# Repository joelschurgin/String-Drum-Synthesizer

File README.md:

# String-Drum-Synthesizer

## Problem
A musical artist brings with them a sense of how to evoke certain emotions or create particular atmospheres, but may lack the technical knowledge to bring it to life. Sound design can be challenging as it involves crafting the unique timbres and textures that define a piece of music, which can be both an art and a science. The learning curve is steep, not only because it requires a grasp of complex technical tools but also because it demands a creative intuition that isn't easily taught. Musicians and producers must learn to navigate a vast array of software and hardware tools, each with its own set of knobs, sliders, and buttons. Understanding how to shape sounds means diving deep into the physics of sound waves, the principles of digital signal processing, and the subtleties of different synthesis methods. This process can feel overwhelming, especially for beginners who might feel lost amidst the jargon and the sheer number of options.

## Solution
Build a synthesizer. The range of sounds are controlled by a set of parameters such as filter cutoffs, oscillator types, low frequency oscillators, etc. The proposed solution is two-fold. The first part of the project is to build emotive knobs that feature descriptive ranges such as soft to aggressive or thin to thick. These knobs would also control the internal parameters of the system to achieve the desired effects on the input sound. The other part is to create a system that records a sound and finds the best way to set the synthesizer's internal parameters to recreate it. The intended work flow of this device for a musical artist is to record a sound, tweak the knobs, and play that sound by pressing a key on a MIDI keyboard. It is up to the musician to record the sound into their own recording software for further manipulation.

# Solution Components
## Subsystem 1: Software Synthesizer
Purpose/Requirements: This subsystem will generate sounds using the Karplus Strong algorithm which features a pulse generator and an echo chamber (modeled with digital delay, feedback, and filtering). When a note is played on a USB keyboard, this component must be able to change the pitch based on which key is pressed. The algorithm’s parameters must be controllable using potentiometers, but several parameters can be determined as a function of one knob. We chose the Karplus Strong algorithm to reduce the computational load, but we are modifying certain aspects to allow for a greater range of sounds. The pulse that we will use is a blend of noise and sine wave oscillator which are added together and distorted. In addition, there will be some soft distortion applied on the output. In addition, the echo chamber will use 3 IIR filters: highpass, lowpass, and a bell. The choice to use IIR filters is to lower the amount of computation.

We made a demo of the synthesizer algorithm using a digital audio workstation in order to play with parameters and determine the names of the emotive knobs. Below are the emotive knobs and how the corresponding synth parameters should change to implement them:

Aggression

- Synth Params: Pulse distortion, output distortion
- Knob Left: Low distortion
- Knob Right: High distortion

Brightness

- Synth Param: Low pass filter cutoff
- Knob Left: 20 Hz
- Knob Right: 20 kHz

Boominess

- Synth Param: High pass Cutoff
- Knob Left: 20 kHz
- Knob Center: Note pitch
- Knob Right: 20 Hz

Dampening

- Synth Param: Bell Q
- Knob Left: High Q
- Knob Right: Low Q

*Not sure what to call this yet, but it affects how the echo chamber resonates. Note: setting this to around 3.6 kHz sounds good, so it could be fine to keep this completely internal and forgo the corresponding knob.

- Synth Param: Bell frequency
- Knob Left: 20 hz
- Knob Right: 20 kHz

Scratchiness

- Synth Param: Length of pulse
- Knob Left: 0
- Knob Center: 1/(Note pitch)
- Knob Right: 4/(Note pitch)

Sharpness

- Synth Param: Mix between pulse noise and oscillator
- Knob Left: Pulse consists of only oscillator
- Knob Right: Pulse consists of only noise

*Strike weight => Corresponds to simulated weight of object striking the string/drum head.

- Synth Param: Pulse oscillator pitch
- Knob Left: 20 kHz
- Knob Right: 20 hz

Notes:
- The value "note pitch" is determined by USB keyboard input.
- Bell gain is fixed and should be set to attenuate the signal.

Components:

- Microprocessor
- DAC
- Potentiometers for parameters (linear, should be able to snap to center position if center value has meaning other should be smooth all the way through)
- USB Port

## Subsystem 3: Amplifier
Purpose/Requirements: This subsystem should output the smallest possible signal to noise ratio through a guitar cable or headphones. In order to achieve this we will experiment with using several inverting op-amp amplifier circuits in parallel and summing them together with an inverting mixer. The gain of each amplifier will be set, but the volume control will be part of the inverting mixer circuit.

Components:

- Mono 1/4in audio jack
- 4 Op-amps
- Logarithmic Potentiometer (for volume control)

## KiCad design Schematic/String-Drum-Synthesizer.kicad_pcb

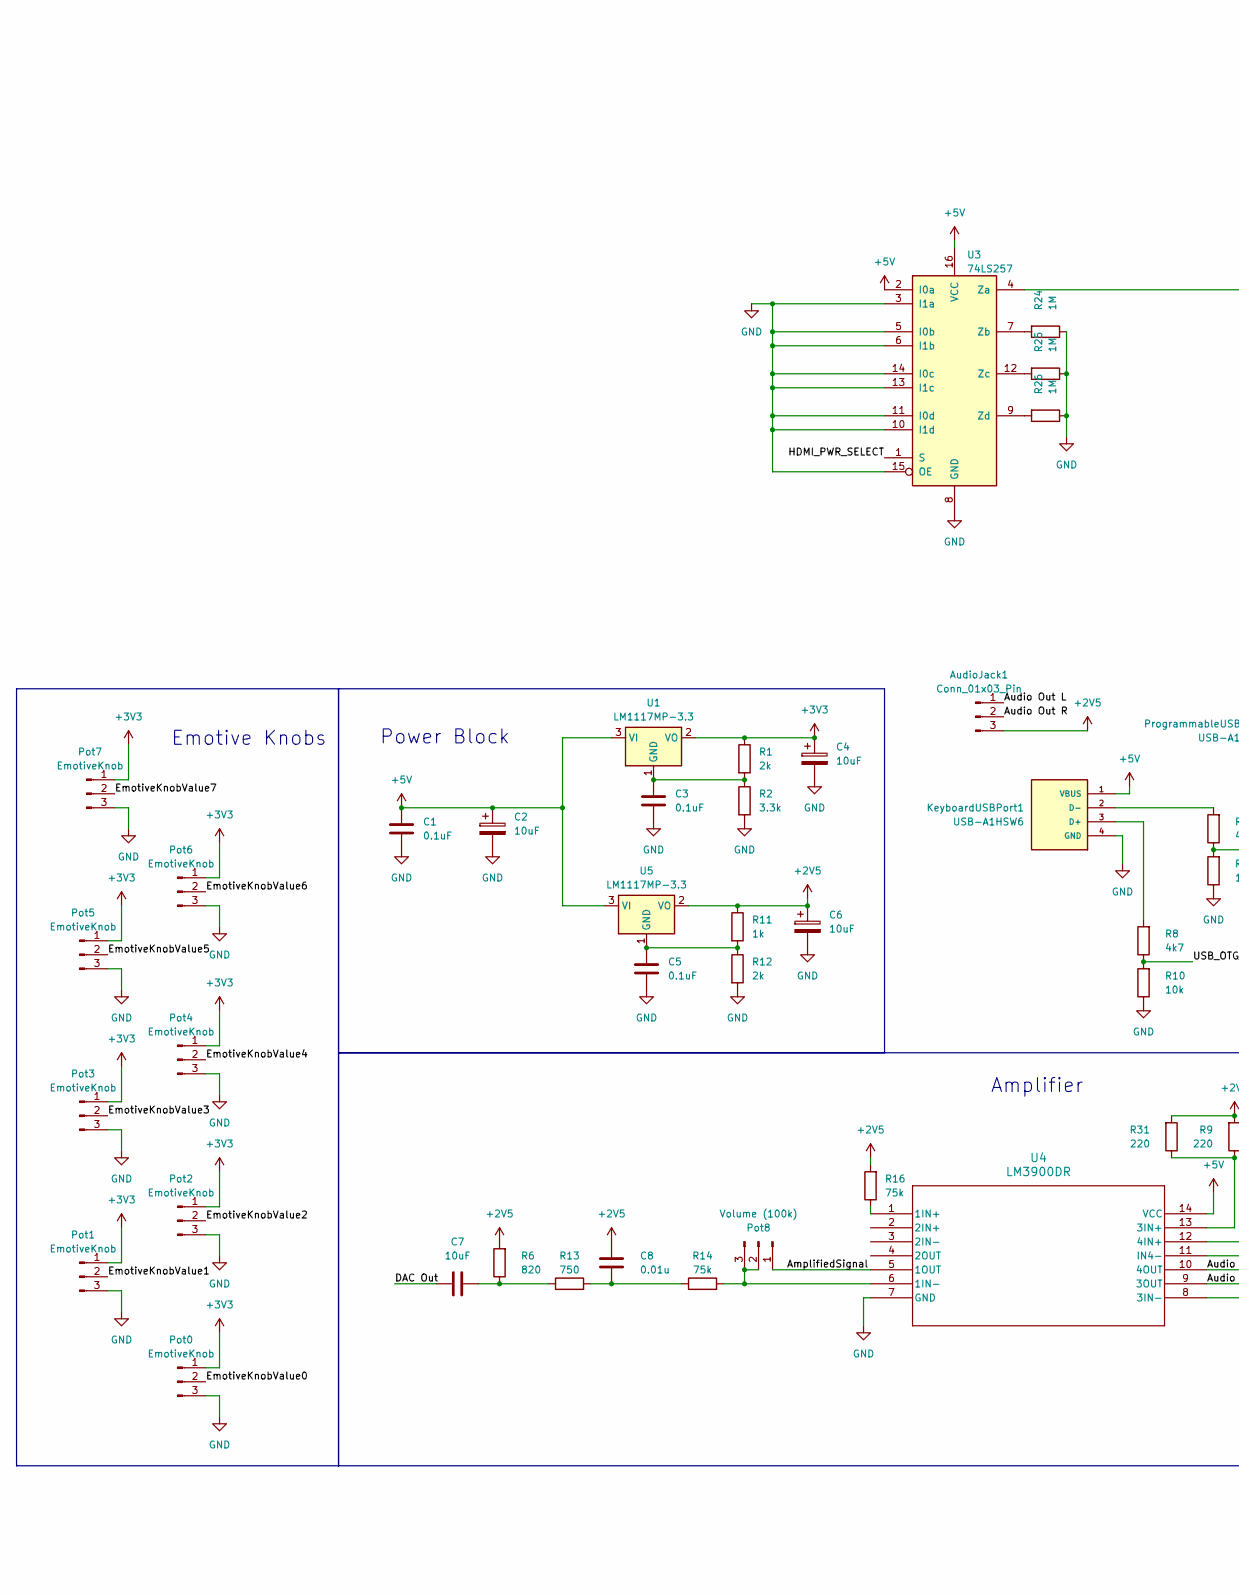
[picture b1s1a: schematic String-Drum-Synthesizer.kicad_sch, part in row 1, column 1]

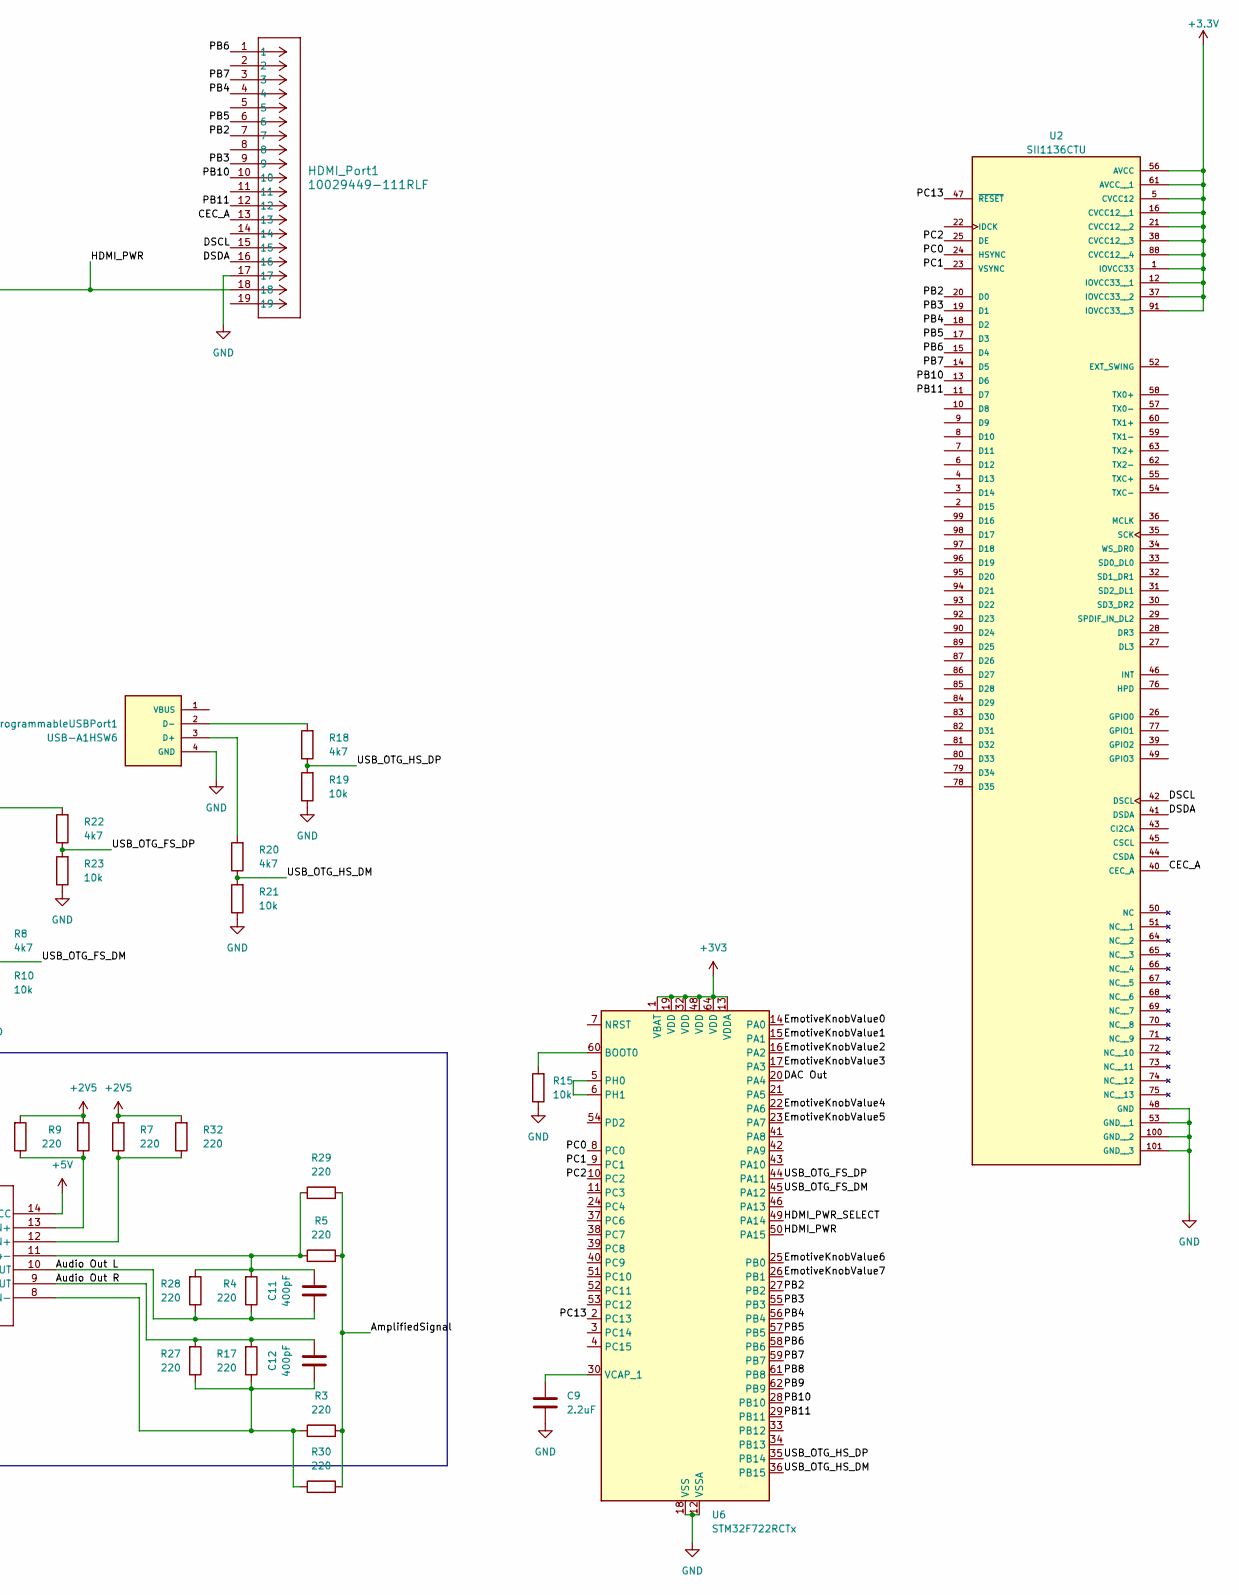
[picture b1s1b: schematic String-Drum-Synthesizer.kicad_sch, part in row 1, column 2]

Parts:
AudioJack1: Conn_01x03_Pin; Molex_KK-254_AE-6410-03A_1x03_P2.54mm_Vertical
C1, C3, C5: 0.1uF; C_Disc_D6.0mm_W4.4mm_P5.00mm
C2, C4, C6, C7: 10uF; CP_Radial_D7.5mm_P2.50mm
C8: 0.01u; C_Disc_D6.0mm_W4.4mm_P5.00mm
C9: 2.2uF; C_Disc_D6.0mm_W4.4mm_P5.00mm
C11, C12: 400pF; C_Disc_D6.0mm_W4.4mm_P5.00mm
HDMI_Port1: 10029449-111RLF; CONN_10029449111_AMP
KeyboardUSBPort1: USB-A1HSW6; OST_USB-A1HSW6; PARTREV A
Pot0, Pot1, Pot2, Pot3, Pot4, Pot5, Pot6, Pot7: EmotiveKnob; Molex_KK-254_AE-6410-03A_1x03_P2.54mm_Vertical
Pot8: Volume (100k); Molex_KK-254_AE-6410-03A_1x03_P2.54mm_Vertical
ProgrammableUSBPort1: USB-A1HSW6; OST_USB-A1HSW6; PARTREV A
R1, R12: 2k; R_Axial_DIN0207_L6.3mm_D2.5mm_P7.62mm_Horizontal
R2: 3.3k; R_Axial_DIN0207_L6.3mm_D2.5mm_P7.62mm_Horizontal
R3, R4, R5, R7, R9, R17, R27, R28, R29, R30, R31, R32: 220; R_Axial_DIN0207_L6.3mm_D2.5mm_P7.62mm_Horizontal
R6: 820; R_Axial_DIN0207_L6.3mm_D2.5mm_P7.62mm_Horizontal
R8, R18, R20, R22: 4k7; R_Axial_DIN0207_L6.3mm_D2.5mm_P7.62mm_Horizontal
R10, R15, R19, R21, R23: 10k; R_Axial_DIN0207_L6.3mm_D2.5mm_P7.62mm_Horizontal
R11: 1k; R_Axial_DIN0207_L6.3mm_D2.5mm_P7.62mm_Horizontal
R13: 750; R_Axial_DIN0207_L6.3mm_D2.5mm_P7.62mm_Horizontal
R14, R16: 75k; R_Axial_DIN0207_L6.3mm_D2.5mm_P7.62mm_Horizontal
R24, R25, R26: 1M; R_Axial_DIN0207_L6.3mm_D2.5mm_P7.62mm_Horizontal
U1, U5: LM1117MP-3.3; SOT-223-3_TabPin2
U2: SII1136CTU; TQFP-100-1EP_14x14mm_P0.5mm_EP5x5mm
U3: 74LS257; DIP-16_W7.62mm_Socket
U4: LM3900DR; DIP-14_W7.62mm_Socket
U6: STM32F722RCTx; LQFP-64_10x10mm_P0.5mm

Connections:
+2V5: AudioJack1.3, C6.1, C8.1, R6.2, R7.2, R9.2, R11.1, R16.2, R31.2, R32.2, U5.2 (VO)
+3.3V: U2.1 (IOVCC33), U2.5 (CVCC12), U2.12 (IOVCC33__1), U2.16 (CVCC12__1), U2.21 (CVCC12__2), U2.37 (IOVCC33__2), U2.38 (CVCC12__3), U2.56 (AVCC), U2.61 (AVCC__1), U2.88 (CVCC12__4), U2.91 (IOVCC33__3)
+3V3: C4.1, Pot0.1, Pot1.1, Pot2.1, Pot3.1, Pot4.1, Pot5.1, Pot6.1, Pot7.1, R1.1, U1.2 (VO), U6.1 (VBAT), U6.13 (VDDA), U6.19 (VDD), U6.32 (VDD), U6.48 (VDD), U6.64 (VDD)
+5V: C1.1, C2.1, KeyboardUSBPort1.1 (VBUS), U1.3 (VI), U3.2 (I0a), U3.16 (VCC), U4.14 (VCC), U5.3 (VI); also elsewhere on the board
/AmplifiedSignal: Pot8.1, R3.2, R5.2, R29.2, R30.2, U4.5 (1OUT); also elsewhere on the board
/Audio Out L: AudioJack1.1, C11.1, R4.1, R28.1, U4.10 (4OUT)
/Audio Out R: AudioJack1.2, C12.2, R17.2, R27.2, U4.9 (3OUT)
/CEC_A: HDMI_Port1.13, U2.40 (CEC_A)
/DAC Out: C7.1, U6.20 (PA4)
/DSCL: HDMI_Port1.15, U2.42 (DSCL)
/DSDA: HDMI_Port1.16, U2.41 (DSDA)
/EmotiveKnobValue0: Pot0.2, U6.14 (PA0)
/EmotiveKnobValue1: Pot1.2, U6.15 (PA1)
/EmotiveKnobValue2: Pot2.2, U6.16 (PA2)
/EmotiveKnobValue3: Pot3.2, U6.17 (PA3)
/EmotiveKnobValue4: Pot4.2, U6.22 (PA6)
/EmotiveKnobValue5: Pot5.2, U6.23 (PA7)
/EmotiveKnobValue6: Pot6.2, U6.25 (PB0)
/EmotiveKnobValue7: Pot7.2, U6.26 (PB1)
/HDMI_PWR: HDMI_Port1.18, U3.4 (Za), U6.50 (PA15); also elsewhere on the board
/HDMI_PWR_SELECT: U3.1 (S), U6.49 (PA14); also elsewhere on the board
/PB2: HDMI_Port1.7, U2.20 (D0), U6.27 (PB2)
/PB3: HDMI_Port1.9, U2.19 (D1), U6.55 (PB3)
/PB4: HDMI_Port1.4, U2.18 (D2), U6.56 (PB4)
/PB5: HDMI_Port1.6, U2.17 (D3), U6.57 (PB5)
/PB6: HDMI_Port1.1, U2.15 (D4), U6.58 (PB6)
/PB7: HDMI_Port1.3, U2.14 (D5), U6.59 (PB7)
/PB8: U6.61 (PB8)
/PB9: U6.62 (PB9)
/PB10: HDMI_Port1.10, U2.13 (D6), U6.28 (PB10)
/PB11: HDMI_Port1.12, U2.11 (D7), U6.29 (PB11)
/PC0: U2.24 (HSYNC), U6.8 (PC0)
/PC1: U2.23 (VSYNC), U6.9 (PC1)
/PC2: U2.25 (DE), U6.10 (PC2)
/PC13: U2.47 (~RESET), U6.2 (PC13)
/USB_OTG_FS_DM: R8.1, R10.2, U6.45 (PA12)
/USB_OTG_FS_DP: R22.1, R23.2, U6.44 (PA11)
/USB_OTG_HS_DM: R20.1, R21.2, U6.36 (PB15)
/USB_OTG_HS_DP: R18.1, R19.2, U6.35 (PB14)
GND: C1.2, C2.2, C3.2, C4.2, C5.2, C6.2, C9.2, HDMI_Port1.17, KeyboardUSBPort1.4 (GND), Pot0.3, Pot1.3, Pot2.3, Pot3.3, Pot4.3, Pot5.3, Pot6.3, Pot7.3, ProgrammableUSBPort1.4 (GND), R2.2, R10.1, R12.2, R15.1, R19.1, R21.1, R23.1, R24.1, R25.1, R26.1, U2.48 (GND), U2.53 (GND__1), U2.100 (GND__2), U2.101 (GND__3), U3.3 (I1a), U3.5 (I0b), U3.6 (I1b), U3.8 (GND), U3.10 (I1d), U3.11 (I0d), U3.13 (I1c), U3.14 (I0c), U3.15 (OE), U4.7 (GND), U6.12 (VSSA), U6.18 (VSS), U6.31 (VSS), U6.47 (VSS), U6.63 (VSS); also elsewhere on the board
unnamed: C7.2, R6.1, R13.1
unnamed: C8.2, R13.2, R14.1
unnamed: KeyboardUSBPort1.3 (D+), R8.2
unnamed: KeyboardUSBPort1.2 (D-), R22.2
unnamed 44: Pot8.2, Pot8.3, R14.2, U4.6 (1IN-); also elsewhere on the board
unnamed: ProgrammableUSBPort1.3 (D+), R20.2
unnamed: ProgrammableUSBPort1.2 (D-), R18.2
unnamed: C3.1, R1.2, R2.1, U1.1 (GND)
unnamed 48: R24.2, U3.7 (Zb); also elsewhere on the board
unnamed 49: R25.2, U3.12 (Zc); also elsewhere on the board
unnamed 50: R26.2, U3.9 (Zd); also elsewhere on the board
unnamed: R16.1, U4.1 (1IN+)
unnamed: R9.1, R31.1, U4.13 (3IN+)
unnamed: C12.1, R3.1, R17.1, R27.1, R30.1, U4.8 (3IN-)
unnamed: R7.1, R32.1, U4.12 (4IN+)
unnamed: C11.2, R4.2, R5.1, R28.2, R29.1, U4.11 (IN4-)
unnamed: C5.1, R11.2, R12.1, U5.1 (GND)
unnamed: R15.2, U6.60 (BOOT0)
unnamed: U6.5 (PH0), U6.6 (PH1)
unnamed: C9.1, U6.30 (VCAP_1)

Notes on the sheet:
Amplifier
Power Block
Emotive Knobs

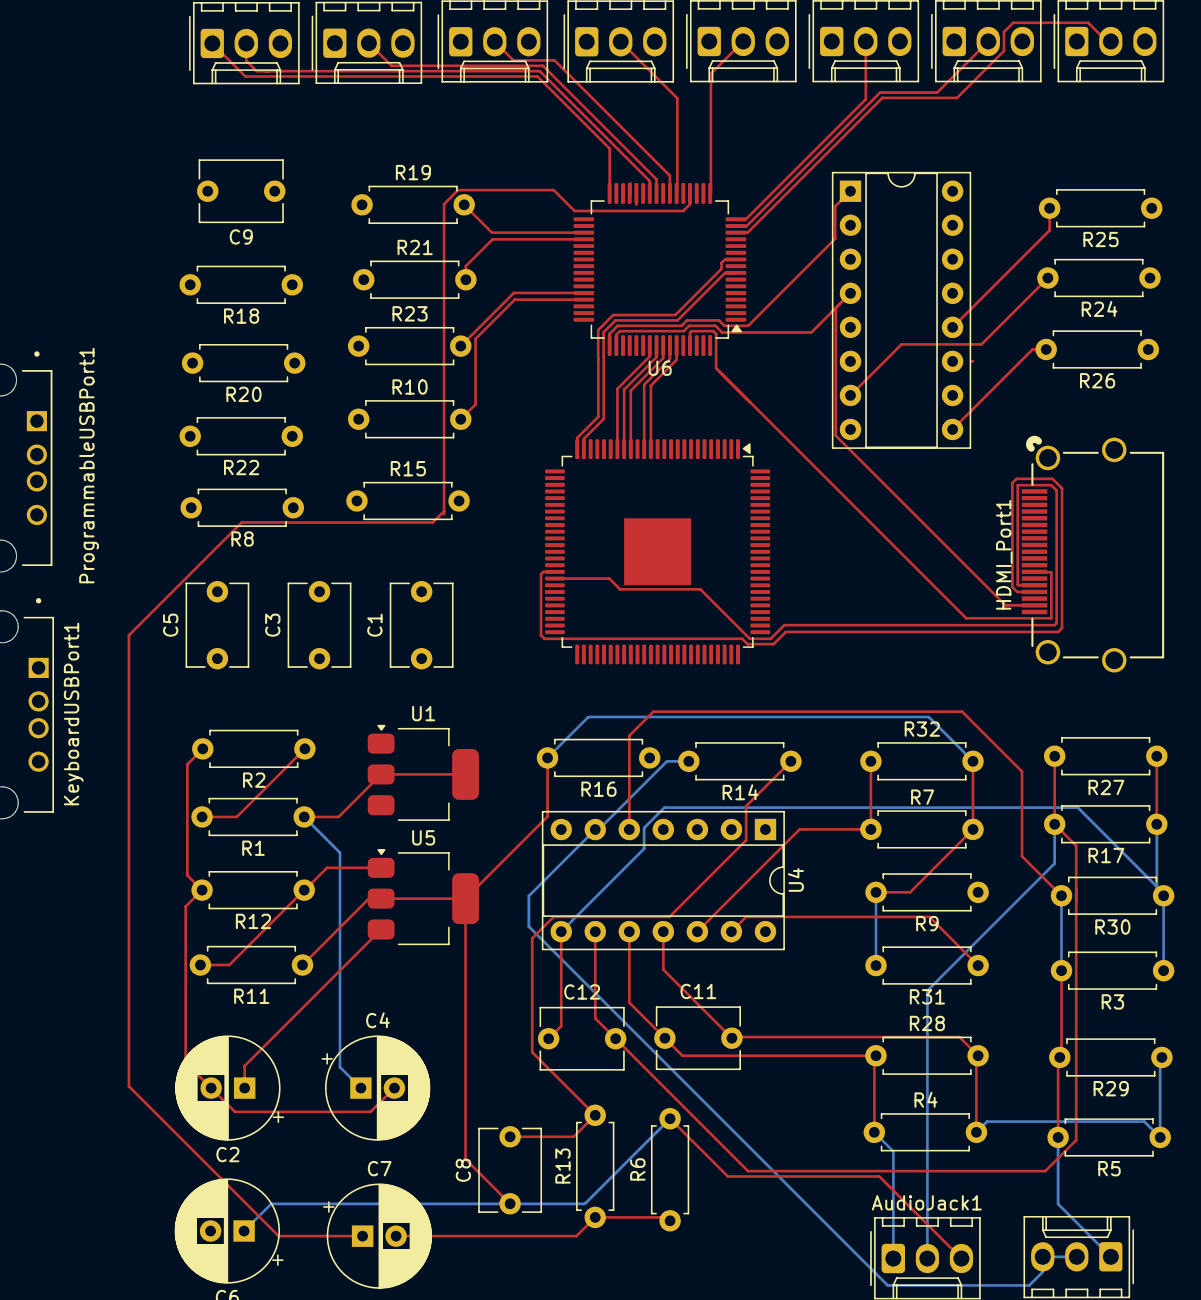
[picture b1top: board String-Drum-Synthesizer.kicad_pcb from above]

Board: 2 copper layers, 62 parts (0 on the bottom side), 58 nets.

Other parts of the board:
74LS257: 74LS257; DIP-16_W7.62mm_Socket
Volume: Volume (100k); Molex_KK-254_AE-6410-03A_1x03_P2.54mm_Vertical

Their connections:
+5V: 74LS257.2 (I0a), 74LS257.16 (VCC); also elsewhere on the board
/AmplifiedSignal: Volume.1; also elsewhere on the board
/HDMI_PWR: 74LS257.4 (Za); also elsewhere on the board
/HDMI_PWR_SELECT: 74LS257.1 (S); also elsewhere on the board
GND: 74LS257.3 (I1a), 74LS257.5 (I0b), 74LS257.6 (I1b), 74LS257.8 (GND), 74LS257.10 (I1d), 74LS257.11 (I0d), 74LS257.13 (I1c), 74LS257.14 (I0c), 74LS257.15 (OE); also elsewhere on the board
unnamed 44: Volume.2, Volume.3; also elsewhere on the board
unnamed 48: 74LS257.7 (Zb); also elsewhere on the board
unnamed 49: 74LS257.12 (Zc); also elsewhere on the board
unnamed 50: 74LS257.9 (Zd); also elsewhere on the board

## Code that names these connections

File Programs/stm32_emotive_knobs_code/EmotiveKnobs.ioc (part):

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Mcu.Name=STM32F401R(D-E)Tx
Mcu.Package=LQFP64
Mcu.UserName=STM32F401RETx
PA0-WKUP.Signal=ADCx_IN0
PA1.Signal=ADCx_IN1
PA11.GPIOParameters=GPIO_Speed,GPIO_PuPd,GPIO_Label
PA11.GPIO_Label=Bit3
PA11.GPIO_PuPd=GPIO_PULLDOWN
PA11.GPIO_Speed=GPIO_SPEED_FREQ_HIGH
PA11.Signal=GPIO_Output
PA12.GPIOParameters=GPIO_Speed,GPIO_PuPd,GPIO_Label
PA12.GPIO_Label=Bit4
PA12.GPIO_PuPd=GPIO_PULLDOWN
PA12.GPIO_Speed=GPIO_SPEED_FREQ_HIGH
PA12.Signal=GPIO_Output
PA2.Signal=ADCx_IN2
PA3.Signal=ADCx_IN3
PA4.Signal=ADCx_IN4
PA5.Signal=ADCx_IN5
PA6.Signal=ADCx_IN6
PA7.Signal=ADCx_IN7
PA8.GPIOParameters=GPIO_Label
PA8.GPIO_Label=Select_A
PA8.Signal=GPIO_Input
PA9.GPIOParameters=GPIO_Label
PA9.GPIO_Label=Select_B
PA9.Signal=GPIO_Input
PB1.GPIOParameters=GPIO_Speed,GPIO_PuPd,GPIO_Label
PB1.GPIO_Label=Bit0
PB1.GPIO_PuPd=GPIO_PULLDOWN
PB1.GPIO_Speed=GPIO_SPEED_FREQ_HIGH
PB1.Signal=GPIO_Output
PB10.GPIOParameters=GPIO_Label
PB10.GPIO_Label=Select_C
PB10.Signal=GPIO_Input
PB12.GPIOParameters=GPIO_Speed,GPIO_PuPd,GPIO_Label
PB12.GPIO_Label=Bit2
PB12.GPIO_PuPd=GPIO_PULLDOWN
PB12.GPIO_Speed=GPIO_SPEED_FREQ_HIGH
PB12.Signal=GPIO_Output
PB2.GPIOParameters=GPIO_Speed,GPIO_PuPd,GPIO_Label
PB2.GPIO_Label=Bit1
PB2.GPIO_PuPd=GPIO_PULLDOWN
PB2.GPIO_Speed=GPIO_SPEED_FREQ_HIGH
PB2.Signal=GPIO_Output
PC5.GPIOParameters=GPIO_Speed,GPIO_PuPd,GPIO_Label
PC5.GPIO_Label=Bit5
PC5.GPIO_PuPd=GPIO_PULLDOWN
PC5.GPIO_Speed=GPIO_SPEED_FREQ_HIGH
PC5.Signal=GPIO_Output
PC6.GPIOParameters=GPIO_Speed,GPIO_PuPd,GPIO_Label
PC6.GPIO_Label=Bit6
PC6.GPIO_PuPd=GPIO_PULLDOWN
PC6.GPIO_Speed=GPIO_SPEED_FREQ_HIGH
PC6.Signal=GPIO_Output
PC8.GPIOParameters=GPIO_Speed,GPIO_PuPd,GPIO_Label
PC8.GPIO_Label=Bit7
PC8.GPIO_PuPd=GPIO_PULLDOWN
PC8.GPIO_Speed=GPIO_SPEED_FREQ_HIGH
PC8.Signal=GPIO_Output
RCC.HSE_VALUE=25000000
RCC.SYSCLKFreq_VALUE=16000000
board=custom

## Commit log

2025-02-10 moving to new repo
